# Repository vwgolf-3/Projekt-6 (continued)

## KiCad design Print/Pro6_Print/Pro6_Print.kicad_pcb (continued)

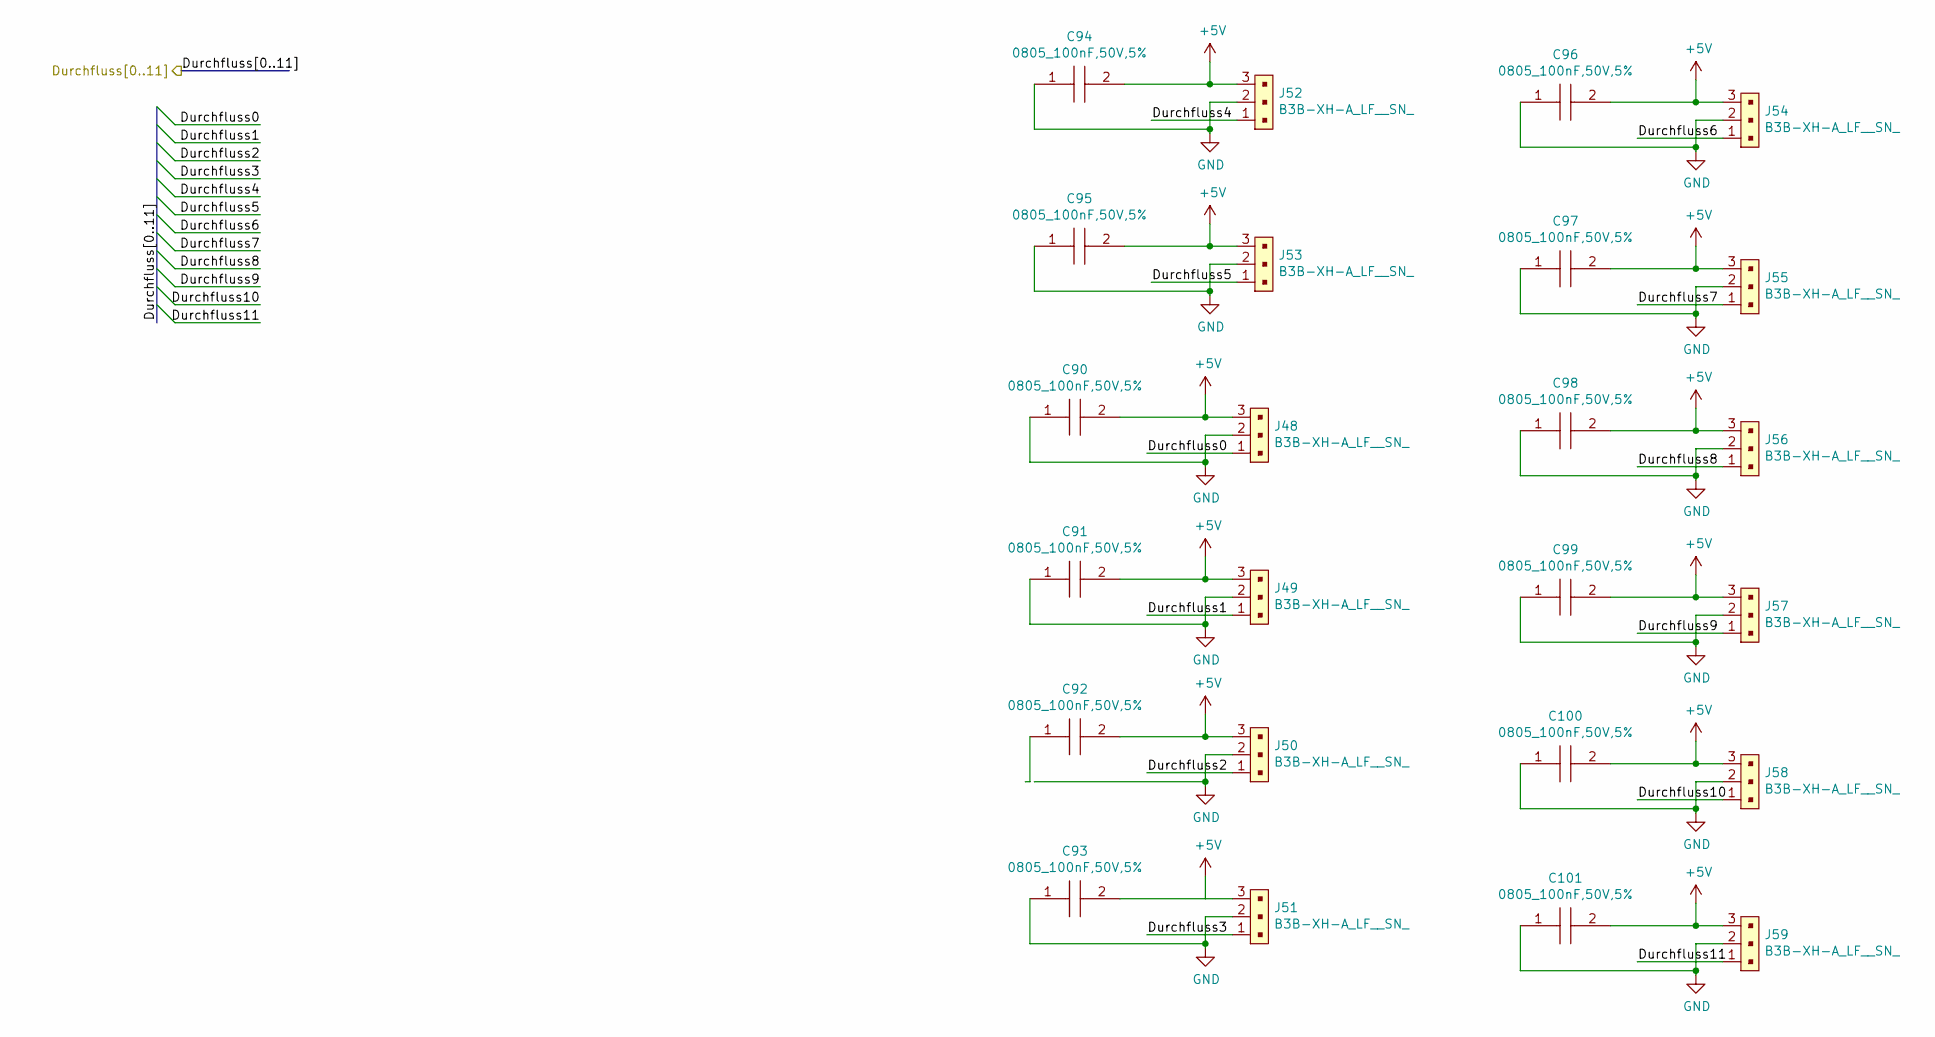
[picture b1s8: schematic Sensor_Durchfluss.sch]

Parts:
C90, C91, C92, C93, C94, C95, C96, C97, C98, C99, C100, C101: 0805_100nF,50V,5%; CAPC2012X88N; Mouser Part Number 80-C0805C104J5R
J48, J49, J50, J51, J52, J53, J54, J55, J56, J57, J58, J59: B3B-XH-A_LF__SN_; JST_XH_B3B-XH-A_1x03_P2.50mm_Vertical; MPN B3B-XH-A(LF)(SN); Digi-Key_PN 455-2248-ND

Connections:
+5V: C90.2, C91.2, C92.2, C93.2, C94.2, C95.2, C96.2, C97.2, C98.2, C99.2, C100.2, C101.2, J48.3, J49.3, J50.3, J51.3, J52.3, J53.3, J54.3, J55.3, J56.3, J57.3, J58.3, J59.3; also elsewhere on the board
/Atmega2560/Durchfluss0: J48.1; also elsewhere on the board
/Atmega2560/Durchfluss1: J49.1; also elsewhere on the board
/Atmega2560/Durchfluss2: J50.1; also elsewhere on the board
/Atmega2560/Durchfluss3: J51.1; also elsewhere on the board
/Atmega2560/Durchfluss4: J52.1; also elsewhere on the board
/Atmega2560/Durchfluss5: J53.1; also elsewhere on the board
/Atmega2560/Durchfluss6: J54.1; also elsewhere on the board
/Atmega2560/Durchfluss7: J55.1; also elsewhere on the board
/Atmega2560/Durchfluss8: J56.1; also elsewhere on the board
/Atmega2560/Durchfluss9: J57.1; also elsewhere on the board
/Atmega2560/Durchfluss10: J58.1; also elsewhere on the board
/Atmega2560/Durchfluss11: J59.1; also elsewhere on the board
GND: C90.1, C91.1, C93.1, C94.1, C95.1, C96.1, C97.1, C98.1, C99.1, C100.1, C101.1, J48.2, J49.2, J50.2, J51.2, J52.2, J53.2, J54.2, J55.2, J56.2, J57.2, J58.2, J59.2; also elsewhere on the board

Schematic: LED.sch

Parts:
C102: 0805_100nF,50V,5%; CAPC2012X88N; Mouser Part Number 80-C0805C104J5R
J60: 1944628; SHDR5W103P0X500_1X5_2700X857X1215P; Mouser Part Number 651-1944628
LED12, LED13, LED14, LED15: AP2012YD_0; AP2012YD; Mouser Part Number 604-AP2012YD
Q22, Q23, Q24, Q25: IRLR8726PBF; D-PAK_TO-252AA__1; Manufacturer_Part_Number IRLR8726PBF; Mouser Part Number 942-IRLR8726PBF
R92, R95, R98, R101: 0805_10Ohm,150V,5%,125mW; RESC2012X60N; Mouser Part Number 603-RC0805JR-1010RL
R93, R96, R99, R102: 0805_100kOhm,150V,125mW,1%-SamacSys_Parts; RESC2012X60N; Mouser Part Number 71-CRCW0805100KFKEAC
R94, R97, R100, R103: CRCW0805330RFKEAC; RESC2012X60N; Mouser Part Number 71-CRCW0805330RFKEAC

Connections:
+12V: C102.1, J60.5, R94.2, R97.2, R100.2, R103.2; also elsewhere on the board
/Atmega2560/LED0: R92.1; also elsewhere on the board
/Atmega2560/LED1: R95.1; also elsewhere on the board
/Atmega2560/LED2: R98.1; also elsewhere on the board
/Atmega2560/LED3: R101.1; also elsewhere on the board
GND: C102.2, Q22.3, Q23.3, Q24.3, Q25.3, R93.2, R96.2, R99.2, R102.2; also elsewhere on the board
unnamed: J60.1, LED12.2 (K), Q22.4
unnamed: J60.2, LED13.2 (K), Q23.4
unnamed: J60.3, LED14.2 (K), Q24.4
unnamed: J60.4, LED15.2 (K), Q25.4
unnamed: LED12.1 (A), R94.1
unnamed: LED13.1 (A), R97.1
unnamed: LED14.1 (A), R100.1
unnamed: LED15.1 (A), R103.1
unnamed: Q22.1, R92.2, R93.1
unnamed: Q23.1, R95.2, R96.1
unnamed: Q24.1, R98.2, R99.1
unnamed: Q25.1, R101.2, R102.1

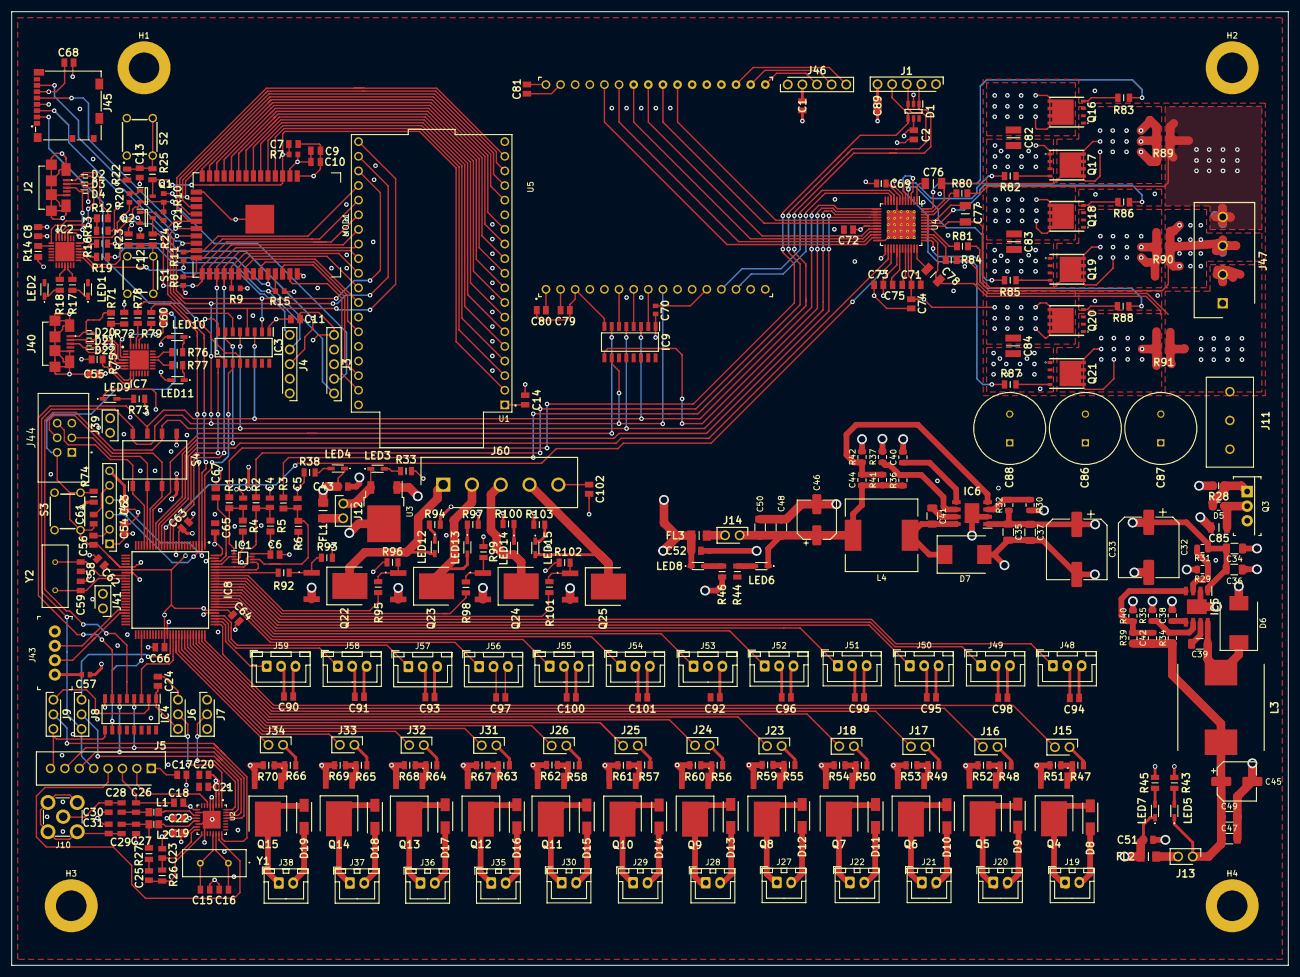
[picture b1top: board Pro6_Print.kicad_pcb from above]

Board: 4 copper layers, 221.8 x 165.7 mm, 359 parts (0 on the bottom side), 273 nets.

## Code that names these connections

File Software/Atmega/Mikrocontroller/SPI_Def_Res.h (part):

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#define FLUSS11_DDR DDRA						// FLUSS10 DDRA
#define FLUSS11_PIN PINA						// FLUSS10 PINA

#define PUMPE0_BIT (1<<2)						// PUMPE0 PIN2
#define PUMPE0_PORT PORTA						// PUMPE0 PORTA
#define PUMPE0_DDR DDRA							// PUMPE0 DDRA
#define PUMPE0_PIN PINA							// PUMPE0 PINA

#define PUMPE1_BIT (1<<3)						// PUMPE1 PIN2
#define PUMPE1_PORT PORTA						// PUMPE1 PORTA
#define PUMPE1_DDR DDRA							// PUMPE1 DDRA
#define PUMPE1_PIN PINA							// PUMPE1 PINA

#define PUMPE2_BIT (1<<4)						// PUMPE2 PIN2
#define PUMPE2_PORT PORTA						// PUMPE2 PORTA
#define PUMPE2_DDR DDRA							// PUMPE2 DDRA
#define PUMPE2_PIN PINA							// PUMPE2 PINA

#define PUMPE3_BIT (1<<5)						// PUMPE3 PIN2
#define PUMPE3_PORT PORTA						// PUMPE3 PORTA
#define PUMPE3_DDR DDRA							// PUMPE3 DDRA
#define PUMPE3_PIN PINA							// PUMPE3 PINA

#define PUMPE4_BIT (1<<6)						// PUMPE4 PIN2
#define PUMPE4_PORT PORTA						// PUMPE4 PORTA
#define PUMPE4_DDR DDRA							// PUMPE4 DDRA
#define PUMPE4_PIN PINA							// PUMPE4 PINA

#define PUMPE5_BIT (1<<7)						// PUMPE5 PIN2
#define PUMPE5_PORT PORTA						// PUMPE5 PORTA
#define PUMPE5_DDR DDRA							// PUMPE5 DDRA
#define PUMPE5_PIN PINA							// PUMPE5 PINA

#define PUMPE_OUTPUT_MASK (PUMPE0_BIT|PUMPE1_BIT|PUMPE2_BIT|PUMPE3_BIT|PUMPE4_BIT|PUMPE5_BIT)

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#define LED_DDR DDRF							// Namensgebung
#define LED_PIN PINF

#define REF0_BIT (1<<0)							// REF0 PIN0
#define REF0_PORT PORTF							// REF0 PORTF
#define REF0_DDR DDRF							// REF0 DDRF
#define REF0_PIN PINF							// REF0 PINF

#define REF1_BIT (1<<1)							// REF0 PIN1
#define REF1_PORT PORTF							// LEDR PORTF
#define REF1_DDR DDRF							// LEDR DDRF
#define REF1_PIN PINF							// LEDR PINF

#define REF2_BIT (1<<2)							// REF0 PIN2
#define REF2_PORT PORTF							// LEDR PORTF
#define REF2_DDR DDRF							// LEDR DDRF
#define REF2_PIN PINF							// LEDR PINF

#define LEDR_BIT (1<<3)							// LEDR PIN3
#define LEDR_PORT PORTF							// LEDR PORTF
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#define PUMPE_DDR2 DDRG							// Namensgebung Timer Register
#define PUMPE_PIN2 PING

#define PUMPE6_BIT (1<<2)						// PUMPE6 PIN2
#define PUMPE6_PORT PORTG						// PUMPE6 PORTG
#define PUMPE6_DDR DDRG							// PUMPE6 DDRG
#define PUMPE6_PIN PING							// PUMPE6 PING

#define SPI_CS_SD_CARD_BIT (1<<5)				// SPI_CS_SD_CARD PIN5
#define SPI_CS_SD_CARD_PORT PORTG				// SPI_CS_SD_CARD PORTG
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#define EN_TMC6200_DDR DDRH						// EN_TMC6200 DDRH
#define EN_TMC6200_PIN PINH						// EN_TMC6200 PINH

#define FAULT_TMC6200_BIT (1<<4)				// DIGITAL1 PIN4
#define FAULT_TMC6200_PORT PORTH				// DIGITAL1 PORTH
#define FAULT_TMC6200_DDR DDRH					// DIGITAL1 DDRH
#define FAULT_TMC6200_PIN PINH					// DIGITAL1 PINH

#define SPI_CS_ESP32_BIT (1<<5)					// SPI_CS_RC522 PIN5
#define SPI_CS_ESP32_PORT PORTH					// SPI_CS_RC522 PORTH
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#define PUMPE_DDR3 DDRJ							// Namensgebung Timer Register
#define PUMPE_PIN3 PINJ							

#define PUMPE11_BIT (1<<2)						// PUMPE11 PIN2
#define PUMPE11_PORT PORTJ						// PUMPE11 PORTJ
#define PUMPE11_DDR DDRJ						// PUMPE11 DDRJ
#define PUMPE11_PIN PINJ						// PUMPE11 PINJ

#define PUMPE10_BIT (1<<3)						// PUMPE10 PIN3
#define PUMPE10_PORT PORTJ						// PUMPE10 PORTJ
#define PUMPE10_DDR DDRJ						// PUMPE10 DDRJ
#define PUMPE10_PIN PINJ						// PUMPE10 PINJ

#define PUMPE9_BIT (1<<4)						// PUMPE9 PIN4
#define PUMPE9_PORT PORTJ						// PUMPE9 PORTJ
#define PUMPE9_DDR DDRJ							// PUMPE9 DDRJ
#define PUMPE9_PIN PINJ							// PUMPE9 PINJ

#define PUMPE8_BIT (1<<5)						// PUMPE8 PIN5
#define PUMPE8_PORT PORTJ						// PUMPE8 PORTJ
#define PUMPE8_DDR DDRJ							// PUMPE8 DDRJ
#define PUMPE8_PIN PINJ							// PUMPE8 PINJ

#define PUMPE7_BIT (1<<6)						// PUMPE7 PIN6
#define PUMPE7_PORT PORTJ						// PUMPE7 PORTJ
#define PUMPE7_DDR DDRJ							// PUMPE7 DDRJ
#define PUMPE7_PIN PINJ							// PUMPE7 PINJ

#define FLUSS9_BIT (1<<7)						// FLUSS9 PIN7
#define FLUSS9_PORT PORTJ						// FLUSS9 PORTJ
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#define NEXTION_DISPLAY_2 2

//Settings TMC4671
#define MOTOR0 0

// Enable / Disable TMC4671
#define ENABLE_TMC4671() SPI_CS_TMC4671_PORT &= ~SPI_CS_TMC4671_BIT
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
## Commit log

2020-02-19 Start
2020-02-20 Ordner
2020-02-23 FAchbericht aufsetzten teil 1
2020-02-23 Fachbericht aufsetzen teil 2
2020-02-23 Fachbericht aufsetzen fertig
2020-02-25 Anpassungen
2020-02-25 Software Mikrocontroller
2020-02-27 Pflichtenheft
2020-03-05 safed
2020-03-05 Projektstrukturplan
2020-03-07 Software
    ESP32
    Atmega
2020-03-07 Software
2020-03-10 nothing
2020-03-12 test
2020-03-12 dätsch
2020-03-26 Teilsysteme anfangen
2020-03-29 Speisungen
2020-04-02 Divers
    Neue Bauteile:
    - USB
    - Wifi
    - RFID
    Doku Schaltungsaufbau:
    - Beleuchtung
2020-04-02 divers
2020-04-02 mini
2020-04-02 Print
2020-04-02 Newer
2020-04-16 Divers
    SW
    Fachbericht
2020-04-22 korrektur
2020-04-25 DiverseArbeiten
2020-04-26 Diverse Arbeiten
2020-04-29 Bilder und Text
2020-04-29 Akku Leer
2020-04-29 last for today
2020-04-30 Motorengruppe
2020-04-30 notfall SW
2020-05-06 sync
2020-06-05 Teilsysteme
2020-06-08 Blockschaltbild
2020-06-14 Listenanzeige
2020-06-14 Bearbeitungsanzeige
2020-06-14 Bearbeitungs/Erstellungsanzeige
2020-06-14 Zutat_Test
2020-06-14 Zutatenliste
2020-06-15 Doku SW und includes
2020-06-17 Posanzeige +/-
2020-07-05 bitz vo allem
2020-07-05 Fachbericht
2020-07-09 Zeugs
2020-07-12 Saves
    - Mikrocontroller SD-Karte UND RFID (Atmega2560)
    -Firmware
    -Testapplikation
2020-08-09 Anpassung Pflichtenheft
2020-08-09 Diverses
2020-08-09 RFID
2020-08-09 RFID fertig
2020-08-26 Display
2020-08-26 Mechanik
2020-08-26 Mechanik2
2020-08-31 Motor
2020-09-02 Not-Commit
2020-09-09 Formatierung
2020-09-11 Verschlimmbesserung
2020-09-11 some citations
2020-09-11 citations and format
2020-09-15 todo
2020-09-17 FB, Factsheet
2020-09-18 korr
2020-09-20 Something
2020-09-20 Quellen
2020-10-03 Quellen bis Mechanik ect
2020-10-05 Korrektur 1 bis Seite 7
2020-10-06 Korrektur bis Seite 10
2020-10-06 KOrrektur bis Seite 15
2020-10-06 KOrrektur bis Seite 23
2020-10-08 Revert "Test"
    This reverts commit f5a81499651c9cd654afd9010efad4103332c430.
2020-10-08 Korrektur bis Seite 30
2020-10-08 Korrektur bis Seit 35
2020-10-11 SW 11.10.2020
2020-10-13 Korrektur bis Seite 42
2020-10-14 safety-comit Software
2020-10-14 Korrektur bis Seite 62
2020-10-15 Fertig Quellen und Korrekturlesen
2020-10-15 Fertig korrigiert
2020-10-16 Various
2020-10-17 Korrektur alles
2020-10-17 Schema in Fachbericht
2020-10-17 Korrekturen FB / SW
2020-10-18 genauso
2020-10-20 Software Ramp FB/SW
2020-10-21 Meeting Fachbericht
2020-10-21 Teilschemas/Namen
2020-10-22 Schema/Mikrocontroller
2020-10-25 meeting
2020-10-27 Abstract/Motorbild
2020-10-27 Überarbeitung
2020-10-28 Software Mittwuch, 28.10.2020 mit Robin getestet
    Motor läuft, Pumpen laufen über RFID-Pins. Enable auf anderen Pin gehängt,
2020-10-28 Fachbericht Gertiser / Inbetriebnahme / Anhang(zum Teil))
2020-10-29 Anhang
2020-10-29 Ausgangslage
2020-10-29 Einleitung
2020-10-29 zwischensp.
2020-10-29 Motor_autoset
2020-10-29 motor Fix autoset und laufen
2020-10-30 Korrekturen
2020-10-30 SW/FB
2020-10-30 Revert "x"
    This reverts commit abab7a9440a40ca750f4763b479b980b78725274.
2020-10-30 Change1
2020-10-30 Fazit und ende
2020-10-30 last fb
2020-10-31 Mir sind fertig Kim gulugulu
2020-11-08 debug praesi
